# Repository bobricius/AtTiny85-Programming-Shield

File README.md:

AtTiny85-Programming-Shield
===========================

For HVSP programing you need externall 12V power and small wire between Attiny85 pin2 and Arduino D9
(bug on PCB)

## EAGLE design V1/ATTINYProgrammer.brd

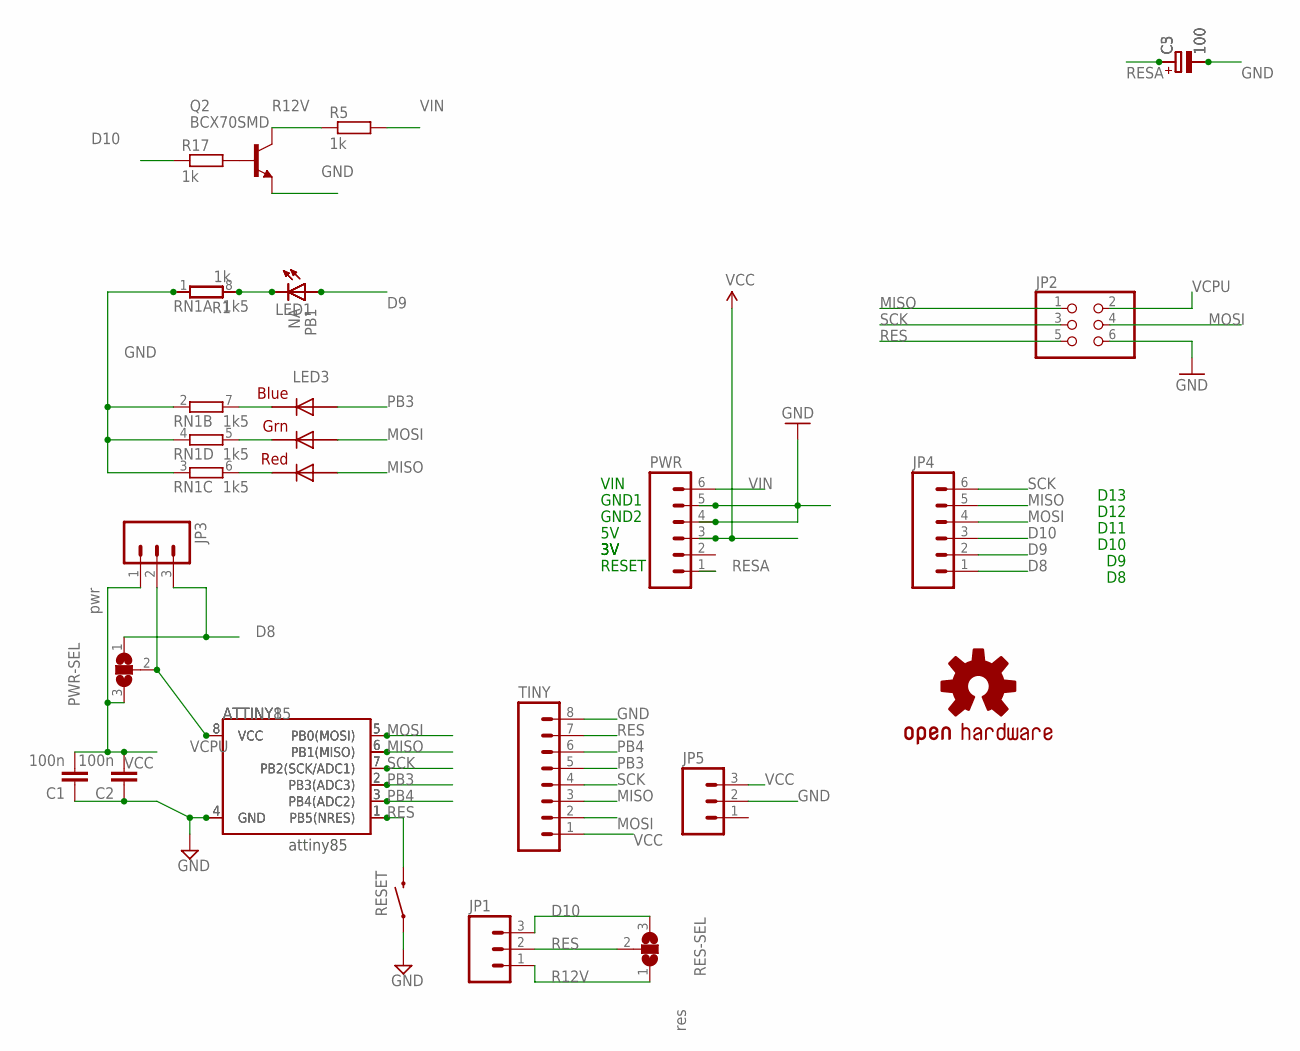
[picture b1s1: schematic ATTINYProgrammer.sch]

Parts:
ATTINY1: ATTINY45; SO08-EIAJ
ATTINY85: ATTINY45DIP8; DIP08
C1: 100n; C0603
C2: 100n; C025-024X044
C3: 100; TT2D4
C5: 100; 153CLV-0405
JP1, JP3: M03PTH; 1X03
JP2: PINHD-2X3; 2X03
JP4: M06LOCK; 1X06_LOCK
JP5: M03LOCK; 1X03_LOCK
LED1: LED3MM
LED3: RGBLED5050
PB1: NA; LED-0603
PWR: M06LOCK; 1X06_LOCK
PWR-SEL: pwr; SJ_2_SMALL
Q2: BCX70SMD; SOT23
R1: 1k; 0204/5@1
R5, R17: 1k; R0603
RES-SEL: res; SJ_2_SMALL
RESET: SWITCH-MOMENTARY-2-SMD-1101NE; TACTILE-SWITCH-1101NE
RN1: 1k5; 0603-ARC
TINY: M08LOCK; 1X08_LOCK
U$2: OSHW-LOGOS; OSHW-LOGO-S

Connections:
D8: JP3.3, JP4.1, PWR-SEL.1
D9: JP4.2, LED1.A, PB1.A
D10: JP1.3, JP4.3, R17.1, RES-SEL.3
GND: ATTINY1.4 (GND), ATTINY85.4 (GND), C1.1, C2.1, C3.-, C5.-, JP2.6, JP5.2, PWR.4, PWR.5, Q2.2 (E), R1.2, RESET.P$1 (1), RN1.1, RN1.2 (1), RN1.3 (1), RN1.4 (1), TINY.8
MISO: ATTINY1.6 (PB1(MISO)), ATTINY85.6 (PB1(MISO)), JP2.1, JP4.5, LED3.2 (RED_A), TINY.3
MOSI: ATTINY1.5 (PB0(MOSI)), ATTINY85.5 (PB0(MOSI)), JP2.4, JP4.4, LED3.1 (GREEN_A), TINY.2
unnamed: LED1.K (C), PB1.C, R1.1, RN1.8 (2)
unnamed: LED3.4 (BLUE_C), RN1.7 (2)
unnamed: LED3.6 (GREEN_C), RN1.5 (2)
unnamed: Q2.1 (B), R17.2
unnamed: LED3.5 (RED_C), RN1.6 (2)
PB3: ATTINY1.2 (PB3(ADC3)), ATTINY85.2 (PB3(ADC3)), LED3.3 (BLUE_A), TINY.5
PB4: ATTINY1.3 (PB4(ADC2)), ATTINY85.3 (PB4(ADC2)), TINY.6
R12V: JP1.1, Q2.3 (C), R5.1, RES-SEL.1
RES: ATTINY1.1 (PB5(NRES)), ATTINY85.1 (PB5(NRES)), JP1.2, JP2.5, RES-SEL.2, RESET.P$2 (2), TINY.7
RESA: C3.+, C5.+, PWR.1
SCK: ATTINY1.7 (PB2(SCK/ADC1)), ATTINY85.7 (PB2(SCK/ADC1)), JP2.3, JP4.6, TINY.4
VCC: C1.2, C2.2, JP3.1, JP5.3, PWR.3, PWR-SEL.3, TINY.1
VCPU: ATTINY1.8 (VCC), ATTINY85.8 (VCC), JP2.2, JP3.2, PWR-SEL.2
VIN: PWR.6, R5.2

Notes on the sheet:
RESET
GND2
GND1
VIN
D13
D12
D11
D10
attiny85

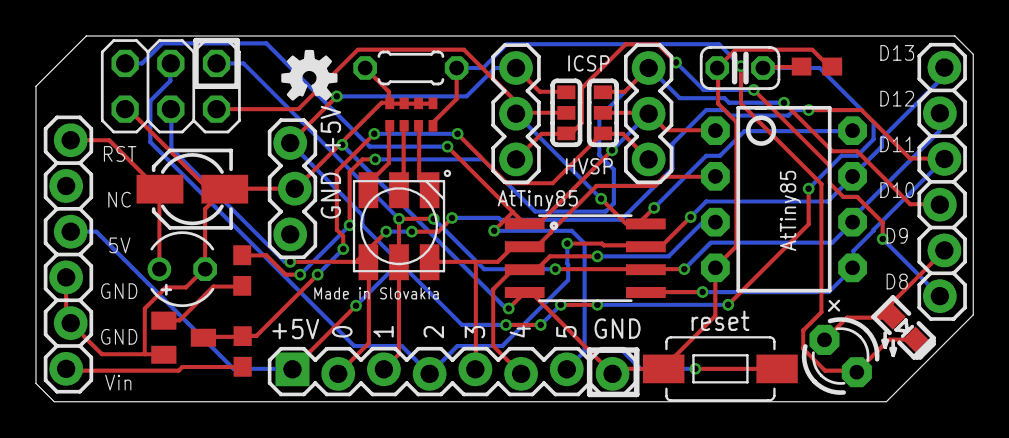
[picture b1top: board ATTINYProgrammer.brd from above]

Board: 2 copper layers, 52.1 x 20.3 mm, 25 parts (0 on the bottom side), 20 nets.

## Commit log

2014-12-17 :octocat: Added .gitattributes & .gitignore files
2014-12-17 firtst upload

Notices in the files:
parts and their libraries:
SparkFun: Licensing: CC v3.0 Share-Alike You are welcome to use this library for commercial purposes.
